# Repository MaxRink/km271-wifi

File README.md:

# KM271-WiFi (WiFi enabled replacement for the KM271)

If you just received a module, you can find help with installation here:

  - [Getting Started Guide](DOC/Getting_Started.md)
  - [Erste Schritte](DOC/Erste_Schritte.md)

This piece of hardware is a direct replacement for the Buderus KM271 to control a buderus heating system with Logamatic 2107 controller board. Maybe other controllers are supported. Please file an issue (or better a PR) if you have my module running in other Buderus heating controllers, so I can add them here.

This hardware and its documentation is released under the *TAPR Open Hardware License* Version 1.0 (May 25, 2007). 
A [copy of the license](LICENSE.txt) is included here or can be accessed in multiple formats on [tapr.org](https://tapr.org/the-tapr-open-hardware-license/). 

For more details, have a look in the:

  * [hardware description](DOC/Hardware%20Description.md)
  * [interactive BOM](https://htmlpreview.github.io/?https://github.com/the78mole/km271-wifi/blob/main/KM217-WiFi/bom/ibom_0.1.0.html)

If you bought the board in my tindie store, you could find a how-to to get it running [here](https://the78mole.de/projects/km271-wifi-howto/)

## Extensions

There is now an Extension to add wired Ethernet to the board. The prototype already works, availability in tindie store will still take some time...

## Order at JLCPCB

Ready-to-upload files for v1.1.0 are in [`KM217-WiFi/production/`](KM217-WiFi/production/) and [`EXTENSIONS/ETH_W5500/production/`](EXTENSIONS/ETH_W5500/production/) (gerber zip, BOM, CPL with LCSC part numbers, iBOM).

| | Main board | ETH add-on |
|---|---|---|
| Layers / thickness | 2 / 1.6 mm | 2 / 1.6 mm |
| Surface finish | ENIG | HASL lead-free |
| Gold fingers | Yes | No |
| Beveling | No (recessed finger tongue, board < 50 mm) | No |
| Assembly | Standard PCBA, both sides | Standard PCBA, both sides |

Details (part swaps, JLC rule checklist, CPL rotation fixes, cost estimate): [DOC/JLCPCB-ordering.md](DOC/JLCPCB-ordering.md).

## Improvements / ToDo

 * Add a OneWire temperature Sensor on the board itself
 * Fix a minor bug with external I2C pull-up (tie them to PCA9306 selectable supply)

## Firmware Management

This project includes a comprehensive firmware management system for easy firmware updates and batch production:

### 🚀 Quick Start

```bash
cd FW
./setup-dev.sh                                    # Setup development environment
uv run scripts/flash_firmware.py                  # List available firmware
uv run scripts/flash_firmware.py blinkenlights    # Flash single device
```

### 📦 Available Firmware Options

- **blinkenlights** - Local PlatformIO test project for hardware validation  
- **km271-esphome** - ESPHome-based KM271 WiFi replacement ([the78mole/ESPhome-KM271-WiFi](https://github.com/the78mole/ESPhome-KM271-WiFi))
- **dewenni-km271** - Feature-rich KM271 firmware ([dewenni/ESP_Buderus_KM271](https://github.com/dewenni/ESP_Buderus_KM271))

All firmware images are automatically downloaded and prepared for flashing using the management scripts.

### 🏭 Batch Production

For manufacturing multiple units:

```bash
uv run scripts/flash_firmware.py blinkenlights --loop
```

- Flash device → Connect next device → Press any key to continue
- Press 'n' to stop and show statistics
- Supports both ESC and 'n' for stopping

### 📖 Documentation

See [`FW/README.md`](FW/README.md) for detailed firmware management documentation, including:

- Setup instructions
- Script usage examples  
- Troubleshooting guide
- Batch production workflows

## 5V Supply Calibration

I decided to set the multiplier very far off the actual value, to make it clear, that you need to calibrate it due to the inaccurate/bad design of the ESP32 ADC with a quite low input impedance and general error.
To calibrate the Buderus 5V voltage monitor, you need to first find out the YAML section of your ESPhome device. It should look like the following:

```yaml
  - platform: adc
    pin: 36
    unit_of_measurement: "V"
    name: "KM217 5V Supply"
    accuracy_decimals: 2
    update_interval: 5s
    attenuation: 6dB
    filters:
      - multiply: 28.1826
      - throttle_average: 60s
```

Now look at the readout of your sensor, say it is 47.3V and measure the real voltage of the 5V supply (e.g. Pin 1 to 7 on the sensor header), say you measure 4.9V. Use the multiplier from your YAML and do the following calculation:

    4.9V / 47.3V * 28.1826 = 2.9196

Replace the multiplier by the calculated value and you will get more exact values, close to the 5V.

## Additional Information

  - [Moles Blog - Reverse Engineering KM271](https://the78mole.de/reverse-engineering-the-buderus-km217/)
  - [Moles Blog - KM271-WiFi Project](https://the78mole.de/projects/km271-wifi-howto/)
  - [KM271-WiFi ESPhome Project (GitHub)](https://github.com/the78mole/ESPhome-KM271-WiFi)
  - [KM271-WiFi WebTools (Flashing)](https://the78mole.github.io/ESPhome-KM271-WiFi/)
  - [KM271-Firmware ESPhome Component (GitHub)](https://github.com/the78mole/esphome_components)

You can buy the module on [Tindie](https://www.tindie.com/products/the78mole/buderus-km217-wifi-replacement/) (if available).

## Star History

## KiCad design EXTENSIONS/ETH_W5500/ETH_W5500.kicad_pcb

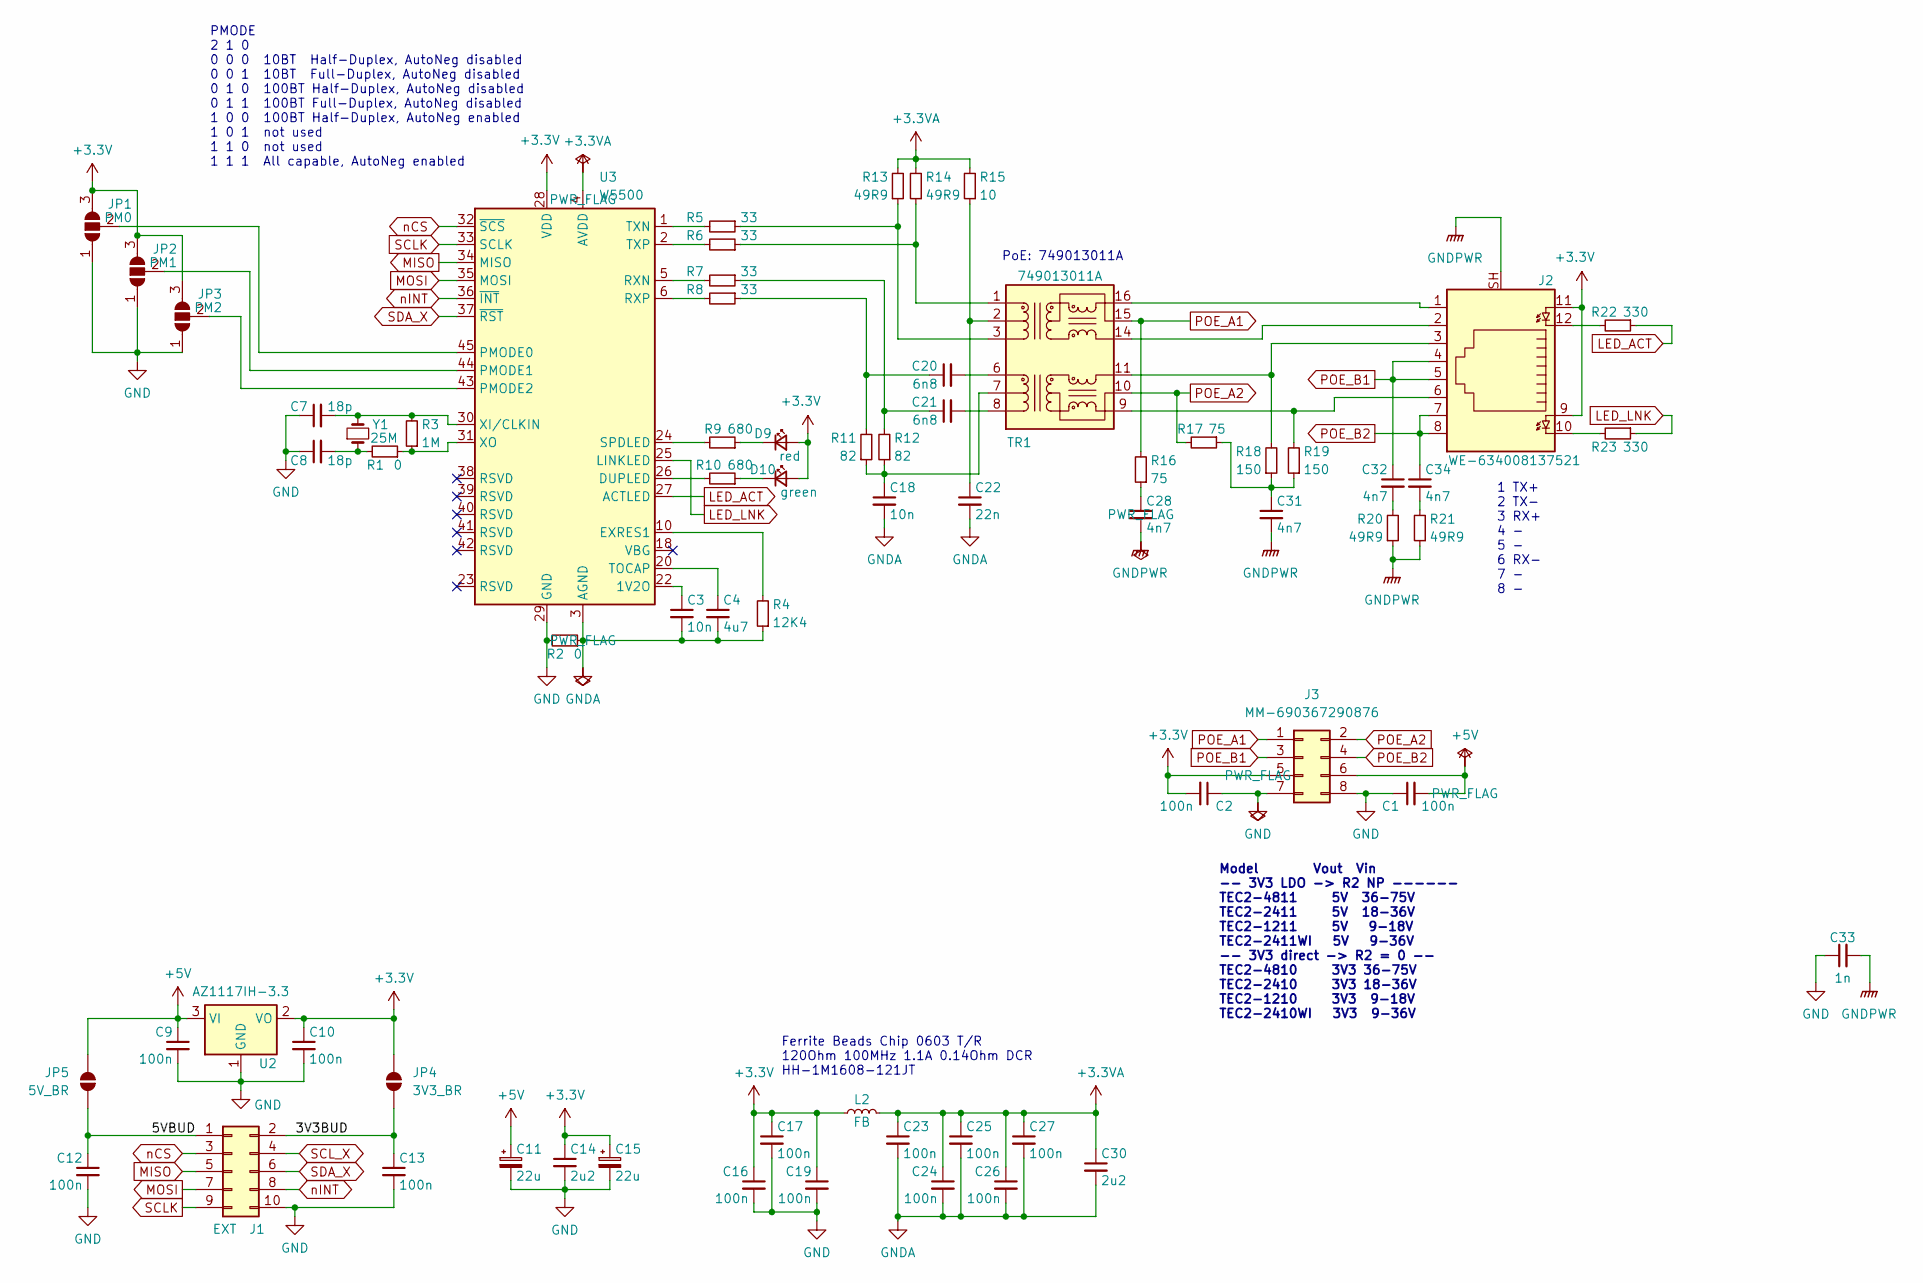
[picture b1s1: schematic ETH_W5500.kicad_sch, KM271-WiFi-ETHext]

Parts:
C1, C2, C9, C10, C12, C13, C16, C17, C19, C23, C24, C25, C26, C27: 100n; C_0603_1608Metric_Pad1.08x0.95mm_HandSolder; LCSC C14663
C3, C18: 10n; C_0603_1608Metric_Pad1.08x0.95mm_HandSolder; LCSC C57112
C4: 4u7; C_0805_2012Metric_Pad1.18x1.45mm_HandSolder; LCSC C1779
C7, C8: 18p; C_0603_1608Metric_Pad1.08x0.95mm_HandSolder; LCSC C1647
C11, C15: 22u; C_0805_2012Metric_Pad1.18x1.45mm_HandSolder; LCSC C45783
C14, C30: 2u2; C_0603_1608Metric_Pad1.08x0.95mm_HandSolder; LCSC C23630
C20, C21: 6n8; C_0603_1608Metric_Pad1.08x0.95mm_HandSolder; LCSC C1631
C22: 22n; C_0603_1608Metric_Pad1.08x0.95mm_HandSolder; LCSC C21122
C28, C31, C32, C34: 4n7; C_0603_1608Metric_Pad1.08x0.95mm_HandSolder; LCSC C53987
C33: 1n; C_1206_3216Metric_Pad1.33x1.80mm_HandSolder; LCSC C9196
D9: red; LED_0603_1608Metric_Pad1.05x0.95mm_HandSolder; LCSC C2286
D10: green; LED_0603_1608Metric_Pad1.05x0.95mm_HandSolder; LCSC C12624
J1: EXT; WE_PinSocket_TH_2x05_P2.54mm_Vertical_SMD; MPN 2.54-2*5P Female Header SMD; LCSC C843271
J2: WE-634008137521; WE-MJ-634008137521; LCSC C6095310
J3: MM-690367290876; WE-MM-690367290876; LCSC C20476862
JP1: PM0; SolderJumper-3_P1.3mm_Open_RoundedPad1.0x1.5mm_NumberLabels
JP2: PM1; SolderJumper-3_P1.3mm_Open_RoundedPad1.0x1.5mm_NumberLabels
JP3: PM2; SolderJumper-3_P1.3mm_Open_RoundedPad1.0x1.5mm_NumberLabels
JP4: 3V3_BR; SolderJumper-2_P1.3mm_Open_RoundedPad1.0x1.5mm
JP5: 5V_BR; SolderJumper-2_P1.3mm_Open_RoundedPad1.0x1.5mm
L2: FB; L_0805_2012Metric_Pad1.05x1.20mm_HandSolder; LCSC C1015
R1, R2: 0; L_0603_1608Metric_Pad1.05x0.95mm_HandSolder; LCSC C21189
R3: 1M; L_0603_1608Metric_Pad1.05x0.95mm_HandSolder; LCSC C22935
R4: 12K4; L_0603_1608Metric_Pad1.05x0.95mm_HandSolder; LCSC C177422
R5, R6, R7, R8: 33; L_0603_1608Metric_Pad1.05x0.95mm_HandSolder; LCSC C23140
R9, R10: 680; L_0603_1608Metric_Pad1.05x0.95mm_HandSolder; LCSC C23228
R11, R12: 82; L_0603_1608Metric_Pad1.05x0.95mm_HandSolder; LCSC C23255
R13, R14, R20, R21: 49R9; L_0603_1608Metric_Pad1.05x0.95mm_HandSolder; LCSC C23185
R15: 10; L_0603_1608Metric_Pad1.05x0.95mm_HandSolder; LCSC C22859
R16, R17: 75; L_0603_1608Metric_Pad1.05x0.95mm_HandSolder; LCSC C4275
R18, R19: 150; L_0603_1608Metric_Pad1.05x0.95mm_HandSolder; LCSC C22808
R22, R23: 330; L_0603_1608Metric_Pad1.05x0.95mm_HandSolder; LCSC C23138
TR1: 749013011A; Transformer_Ethernet_Wuerth_749013011A; LCSC C7193798
U2: AZ1117IH-3.3; SOT-223-3_TabPin2; MPN AZ1117IH-3.3TRG1; LCSC C108495
U3: W5500; LQFP-48_7x7mm_P0.5mm; LCSC C32843
Y1: 25M; Crystal_SMD_HC49-SD; MPN ABLS2-25.000MHZ-D4YF-T; LCSC C596824

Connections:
+3.3V: C2.2, C10.1, C14.1, C15.1, C16.1, C17.1, C19.1, D9.2 (A), D10.2 (A), J2.9, J2.11, J3.5, JP1.3 (B), JP2.3 (B), JP3.3 (B), JP4.1 (A), L2.1, U2.2 (VO), U3.28 (VDD)
+3.3VA: C23.1, C24.1, C25.1, C26.1, C27.1, C30.1, L2.2, R13.2, R14.2, R15.2, U3.4 (AVDD), U3.8 (AVDD), U3.11 (AVDD), U3.15 (AVDD), U3.17 (AVDD), U3.21 (AVDD)
+5V: C1.2, C9.1, C11.1, J3.6, JP5.1 (A), U2.3 (VI)
/3V3BUD: C13.1, J1.2, JP4.2 (B)
/5VBUD: C12.1, J1.1, JP5.2 (B)
GND: C1.1, C2.1, C7.1, C8.1, C9.2, C10.2, C11.2, C12.2, C13.2, C14.2, C15.2, C16.2, C17.2, C19.2, C33.1, J1.10, J3.7, J3.8, JP1.1 (A), JP2.1 (A), JP3.1 (A), R2.2, U2.1 (GND), U3.29 (GND)
GNDA: C3.2, C4.2, C18.2, C22.2, C23.2, C24.2, C25.2, C26.2, C27.2, C30.2, R2.1, R4.1, U3.3 (AGND), U3.9 (AGND), U3.14 (AGND), U3.16 (AGND), U3.19 (AGND), U3.48 (AGND)
GNDPWR: C28.2, C31.2, C33.2, J2.SH, R20.1, R21.1
LED_ACT: R22.1, U3.27 (ACTLED)
LED_LNK: R23.1, U3.25 (LINKLED)
MISO: J1.5, U3.34 (MISO)
MOSI: J1.7, U3.35 (MOSI)
unnamed: C8.2, R1.2, Y1.1
unnamed: C20.1, R8.1, R11.2
unnamed: C21.1, R7.1, R12.2
unnamed: C28.1, R16.1
unnamed: C31.1, R17.1, R18.1, R19.1
unnamed: C32.2, R20.2
unnamed: C34.2, R21.2
unnamed: D9.1 (K), R9.1
unnamed: D10.1 (K), R10.1
unnamed: J2.10, R23.2
unnamed: J2.12, R22.2
unnamed: JP1.2 (C), U3.45 (PMODE0)
unnamed: JP2.2 (C), U3.44 (PMODE1)
unnamed: JP3.2 (C), U3.43 (PMODE2)
unnamed: C18.1, R11.1, R12.1, TR1.7 (C_RD)
unnamed: C22.1, R15.1, TR1.2 (C_TD)
unnamed: C20.2, TR1.6 (RD+)
unnamed: C21.2, TR1.8 (RD-)
unnamed: J2.3, R18.2, TR1.11 (RX+)
unnamed: J2.6, R19.2, TR1.9 (RX-)
unnamed: R6.1, R14.1, TR1.1 (TD+)
unnamed: R5.1, R13.1, TR1.3 (TD-)
unnamed: J2.1, TR1.16 (TX+)
unnamed: J2.2, TR1.14 (TX-)
unnamed: C3.1, U3.22 (1V2O)
unnamed: R10.2, U3.26 (DUPLED)
unnamed: R4.2, U3.10 (EXRES1)
unnamed: R7.2, U3.5 (RXN)
unnamed: R8.2, U3.6 (RXP)
unnamed: R9.2, U3.24 (SPDLED)
unnamed: C4.1, U3.20 (TOCAP)
unnamed: R5.2, U3.1 (TXN)
unnamed: R6.2, U3.2 (TXP)
unnamed: C7.2, R3.2, U3.30 (XI/CLKIN), Y1.2
unnamed: R1.1, R3.1, U3.31 (XO)
POE_A1: J3.1, R16.2, TR1.15 (C_TX)
POE_A2: J3.2, R17.2, TR1.10 (C_RX)
POE_B1: C32.1, J2.4, J2.5, J3.3
POE_B2: C34.1, J2.7, J2.8, J3.4
SCLK: J1.9, U3.33 (SCLK)
SCL_X: J1.4
SDA_X: J1.6, U3.37 (~RST)
nCS: J1.3, U3.32 (~SCS)
nINT: J1.8, U3.36 (~INT)

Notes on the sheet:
PMODE 2 1 0 0 0 0 10BT Half-Duplex, AutoNeg disabled 0 0 1 10BT Full-Duplex, AutoNeg disabled 0 1 0 100BT Half-Duplex, AutoNeg disabled 0 1 1 100BT Full-Duplex, AutoNeg disabled 1 0 0 100BT Half-Duplex, AutoNeg enabled 1 0 1 not used 1 1 0 not used 1 1 1 All capable, AutoNeg enabled
PoE: 749013011A
Ferrite Beads Chip 0603 T/R 120Ohm 100MHz 1.1A 0.14Ohm DCR HH-1M1608-121JT
Model Vout Vin -- 3V3 LDO -> R2 NP ------ TEC2-4811 5V 36-75V TEC2-2411 5V 18-36V TEC2-1211 5V 9-18V TEC2-2411WI 5V 9-36V -- 3V3 direct -> R2 = 0 -- TEC2-4810 3V3 36-75V TEC2-2410 3V3 18-36V TEC2-1210 3V3 9-18V TEC2-2410WI 3V3 9-36V
1 TX+ 2 TX- 3 RX+ 4 - 5 - 6 RX- 7 - 8 -

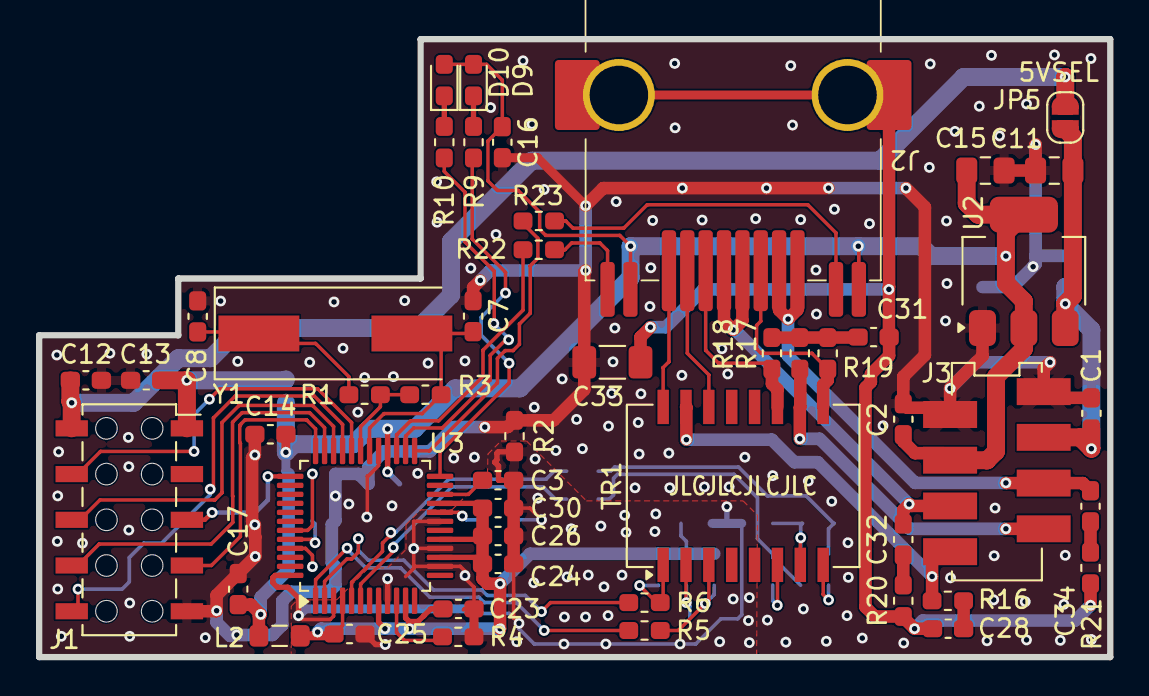
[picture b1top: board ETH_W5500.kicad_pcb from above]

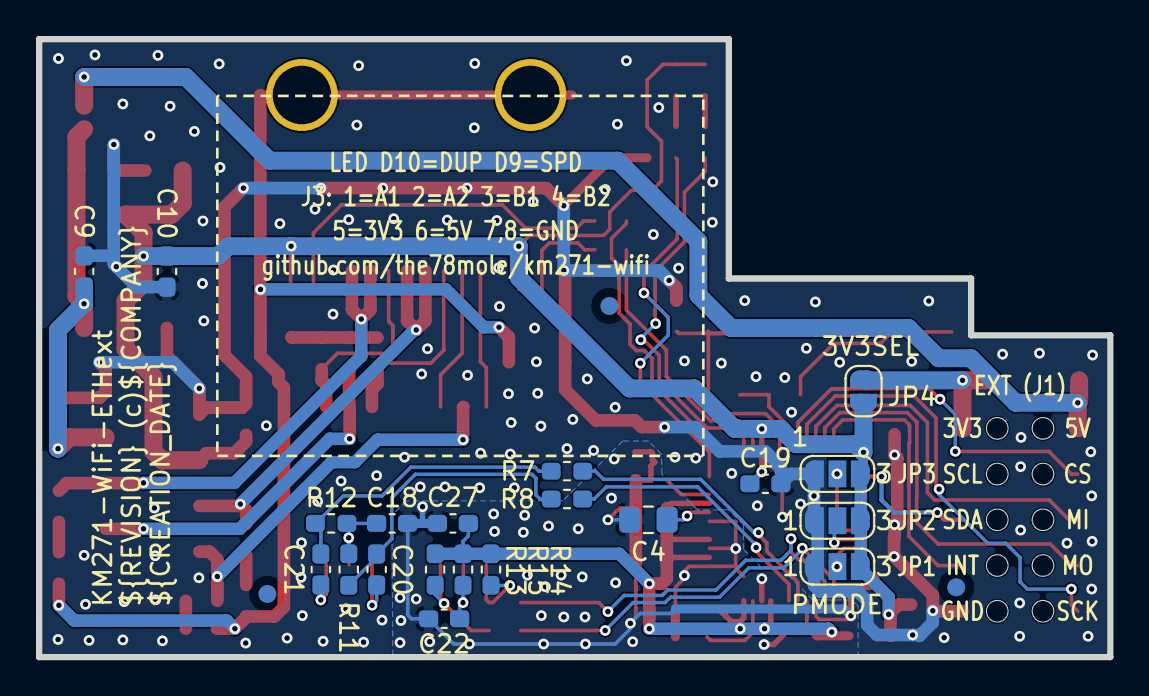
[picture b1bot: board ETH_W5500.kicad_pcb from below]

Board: 2 copper layers, 59.5 x 34.3 mm, 72 parts (23 on the bottom side), 55 nets.

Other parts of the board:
FID1, FID2, FID3: Fiducial_1mm_Mask2mm

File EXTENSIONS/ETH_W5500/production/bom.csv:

Designator,Footprint,Quantity,Value,LCSC Part #
"C1, C10, C12, C13, C16, C17, C19, C2, C23, C24, C25, C26, C27, C9",0603,14,100n,C14663
"C11, C15",0805,2,22u,C45783
"C14, C30",0603,2,2u2,C23630
"C18, C3",0603,2,10n,C57112
"C20, C21",0603,2,6n8,C1631
C22,0603,1,22n,C21122
"C28, C31, C32, C34",0603,4,4n7,C53987
C33,1206,1,1n,C9196
C4,0805,1,4u7,C1779
"C7, C8",0603,2,18p,C1647
D10,0603,1,green,C12624
D9,0603,1,red,C2286
J1,WE_PinSocket_TH_2x05_P2.54mm_Vertical_SMD,1,EXT,C843271
J2,WE-MJ-634008137521,1,WE-634008137521,C6095310
J3,WE-MM-690367290876,1,MM-690367290876,C20476862
L2,0805,1,FB,C1015
"R1, R2",0603,2,0,C21189
"R10, R9",0603,2,680,C23228
"R11, R12",0603,2,82,C23255
"R13, R14, R20, R21",0603,4,49R9,C23185
R15,0603,1,10,C22859
"R16, R17",0603,2,75,C4275
"R18, R19",0603,2,150,C22808
"R22, R23",0603,2,330,C23138
R3,0603,1,1M,C22935
R4,0603,1,12K4,C177422
"R5, R6, R7, R8",0603,4,33,C23140
TR1,Transformer_Ethernet_Wuerth_749013011A,1,749013011A,C7193798
U2,SOT-223-3_TabPin2,1,AZ1117IH-3.3,C108495
U3,LQFP-48_7x7mm_P0.5mm,1,W5500,C32843
Y1,Crystal_SMD_HC49-SD,1,25M,C596824

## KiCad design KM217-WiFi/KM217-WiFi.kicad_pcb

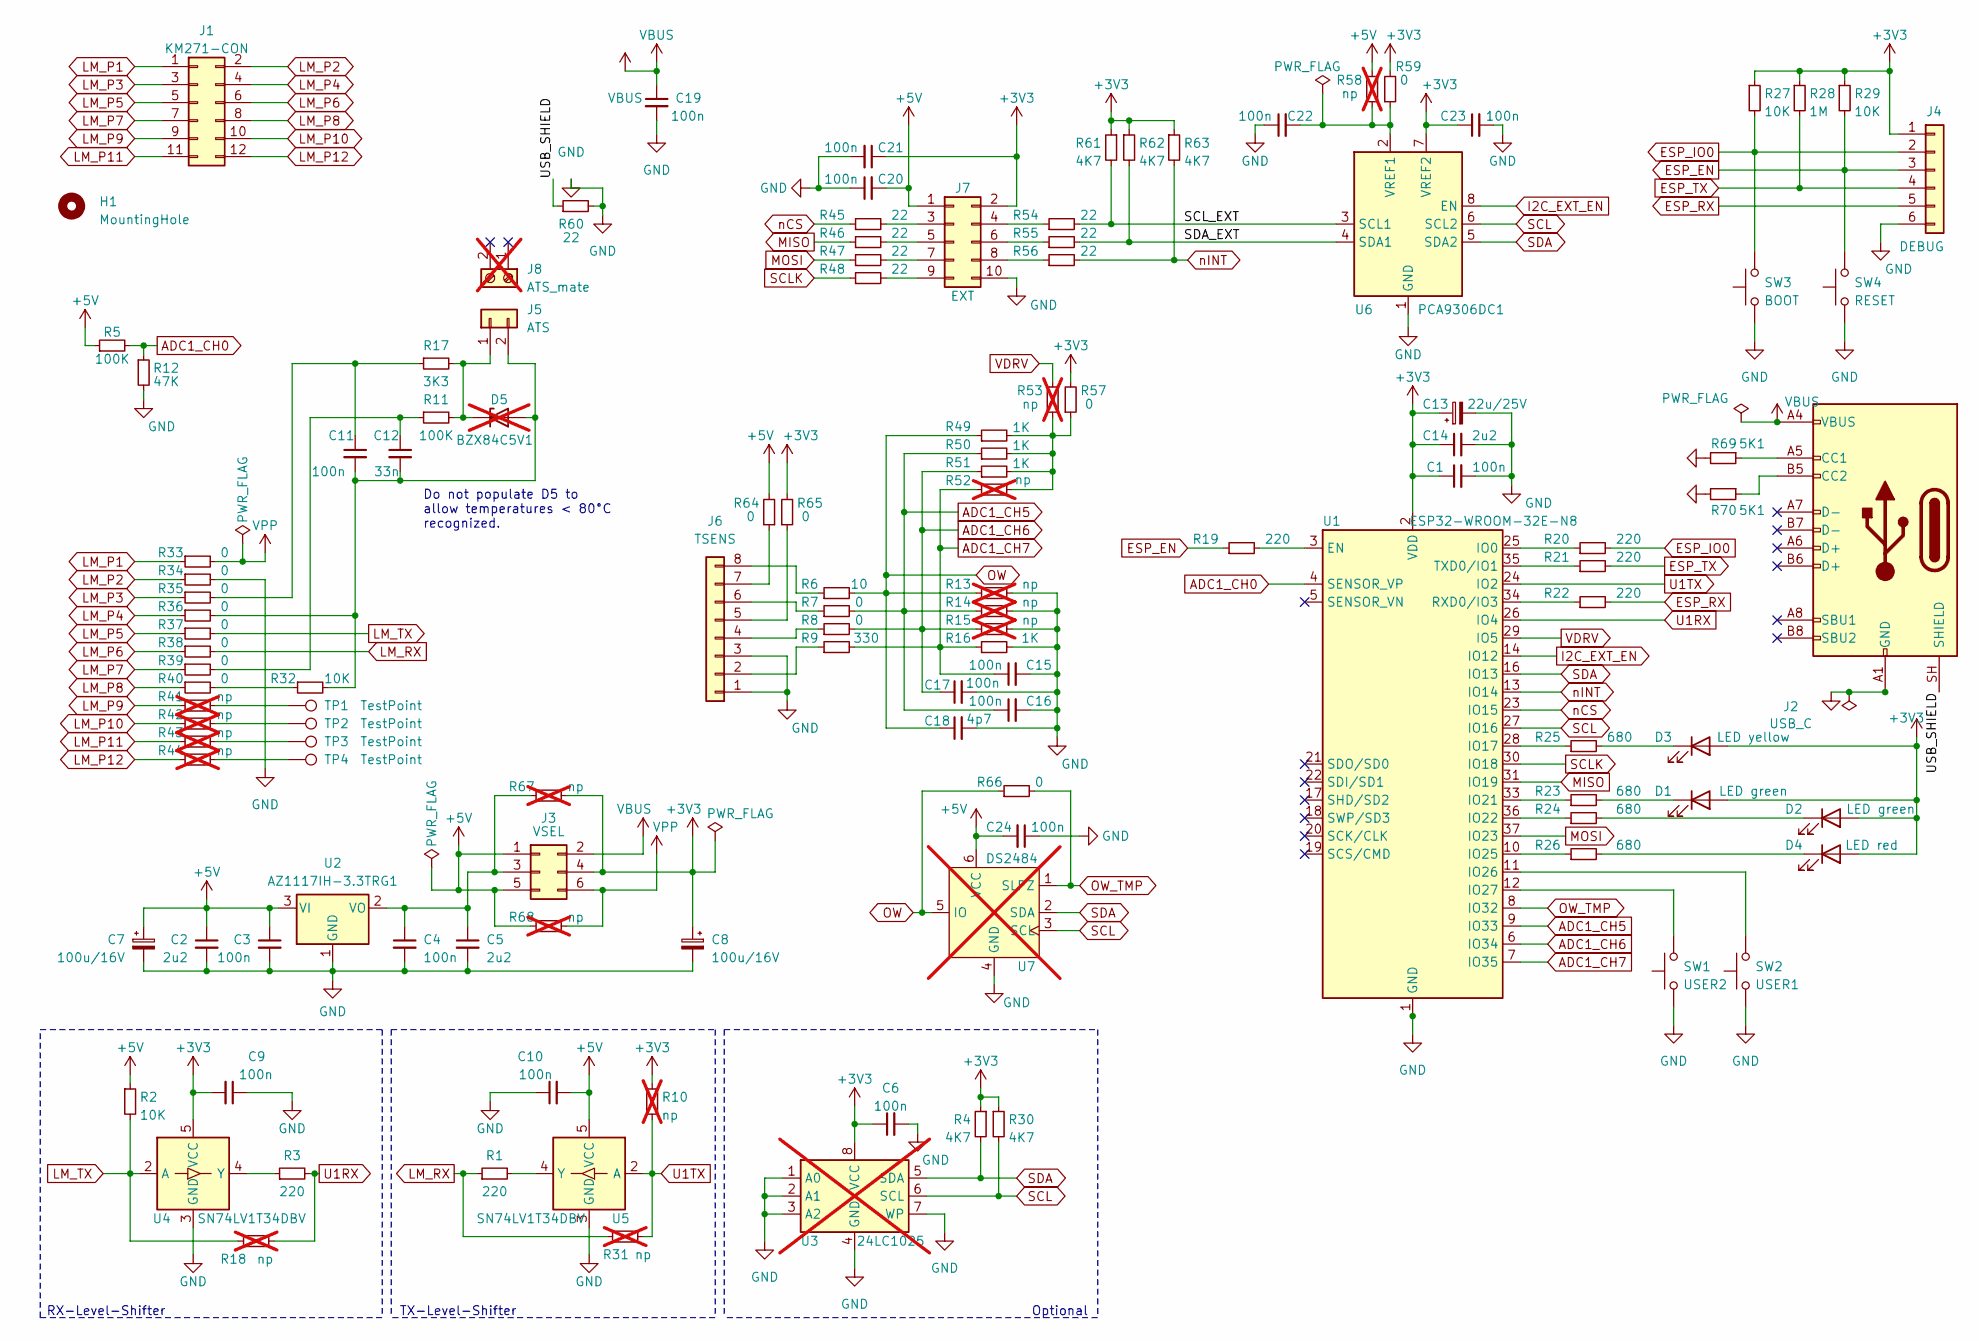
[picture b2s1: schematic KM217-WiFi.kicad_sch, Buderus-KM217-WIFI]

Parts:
C1, C3, C4, C6, C9, C10, C11, C15, C16, C17, C19, C20, C21, C22, C23, C24: 100n; C_0603_1608Metric_Pad1.08x0.95mm_HandSolder; MPN C0603_100n; LCSC C14663
C2, C5, C14: 2u2; C_0603_1608Metric_Pad1.08x0.95mm_HandSolder; MPN C0603_2u2; LCSC C23630
C7, C8: 100u/16V; CP_Elec_6.3x5.4_Nichicon; MPN UWT1C101MCL1GB; LCSC C340722
C12: 33n; C_0603_1608Metric_Pad1.08x0.95mm_HandSolder; MPN C0603_33n; LCSC C21117
C13: 22u/25V; C_1812_4532Metric_Pad1.57x3.40mm_HandSolder; MPN C4532X7R1E226MT000N; LCSC C76690
C18: 4p7; C_0603_1608Metric_Pad1.08x0.95mm_HandSolder; MPN C0603_4p7; LCSC C1669
D1, D2: LED green; LED_0603_1608Metric_Pad1.05x0.95mm_HandSolder; MPN D0603_LED_green; LCSC C12624
D3: LED yellow; LED_0603_1608Metric_Pad1.05x0.95mm_HandSolder; MPN D0603_LED_yellow; LCSC C2287
D4: LED red; LED_0603_1608Metric_Pad1.05x0.95mm_HandSolder; MPN D0603_LED_red; LCSC C2286
D5: BZX84C5V1; D_SOT-23_ANK; MPN BZX84C5V1-7-F; Digikey BZX84C5V1-7-F; not fitted
H1: MountingHole; MountingHole_3.2mm_M3_DIN965
J1: KM271-CON; LM2107_ComModuleCon; MPN PCB gold fingers
J2: USB_C; USB_C_Receptacle_HRO_TYPE-C-31-M-12; MPN TYPE-C-31-M-12; LCSC C165948
J3: VSEL; PinHeader_2x03_P2.54mm_Vertical_SMD; MPN HX PZ2.54-2x3P TP; LCSC C32713283
J4: DEBUG; PinHeader_2x03_P2.54mm_Horizontal; MPN HX PZ2.54-2x3P WC-A; LCSC C41417351
J5: ATS; PhoenixContact_MSTBA_2,5_2-G-5,08_1x02_P5.08mm_Horizontal; MPN 1757242; LCSC C90074
J6: TSENS; WAGO 2086-1208; MPN 2086-1208; LCSC C6074290
J7: EXT; PinHeader_2x05_P2.54mm_Vertical_SMD; MPN 54202-G0805LF; LCSC C3330868
J8: ATS_mate; MPN CTB9202/2; not fitted
R1, R3, R19, R20, R21, R22: 220; R_0603_1608Metric_Pad0.98x0.95mm_HandSolder; MPN R0603_220; LCSC C22962
R2, R27, R29, R32: 10K; R_0603_1608Metric_Pad0.98x0.95mm_HandSolder; MPN R0603_10K; LCSC C25804
R4, R30, R61, R62, R63: 4K7; R_0603_1608Metric_Pad0.98x0.95mm_HandSolder; MPN R0603_4K7; LCSC C23162
R5, R11: 100K; R_0603_1608Metric_Pad0.98x0.95mm_HandSolder; MPN R0603_100K; LCSC C25803
R6: 10; R_0603_1608Metric_Pad0.98x0.95mm_HandSolder; MPN R0603_10; LCSC C22859
R7, R8, R33, R34, R35, R36, R37, R38, R39, R40, R57, R59, R64, R65, R66: 0; R_0603_1608Metric_Pad0.98x0.95mm_HandSolder; MPN R0603_0; LCSC C21189
R9: 330; R_0603_1608Metric_Pad0.98x0.95mm_HandSolder; MPN R0603_330; LCSC C23138
R10, R13, R14, R15, R18, R31, R41, R42, R43, R44, R52, R53, R58, R67, R68: np; R_0603_1608Metric_Pad0.98x0.95mm_HandSolder; MPN np; not fitted
R12: 47K; R_0603_1608Metric_Pad0.98x0.95mm_HandSolder; MPN R0603_47K; LCSC C25819
R16, R49, R50, R51: 1K; R_0603_1608Metric_Pad0.98x0.95mm_HandSolder; MPN R0603_1K; LCSC C21190
R17: 3K3; R_0603_1608Metric_Pad0.98x0.95mm_HandSolder; MPN R0603_3K3; LCSC C22978
R23, R24, R25, R26: 680; R_0603_1608Metric_Pad0.98x0.95mm_HandSolder; MPN R0603_680; LCSC C23228
R28: 1M; R_0603_1608Metric_Pad0.98x0.95mm_HandSolder; MPN R0603_1M; LCSC C22935
R45, R46, R47, R48, R54, R55, R56, R60: 22; R_0603_1608Metric_Pad0.98x0.95mm_HandSolder; MPN R0603_22; LCSC C23345
R69, R70: 5K1; R_0603_1608Metric_Pad0.98x0.95mm_HandSolder; LCSC C23186
SW1: USER2; SW_SPST_B3SL-1002P; MPN B3SL-1002P; LCSC C306880
SW2: USER1; SW_SPST_B3SL-1002P; MPN B3SL-1002P; LCSC C306880
SW3: BOOT; SW_SPST_B3SL-1002P; MPN B3SL-1002P; LCSC C306880
SW4: RESET; SW_SPST_B3SL-1002P; MPN B3SL-1002P; LCSC C306880
TP1, TP2, TP3, TP4: TestPoint; TestPoint_Pad_D2.0mm
U1: ESP32-WROOM-32E-N8; ESP32-WROOM-32; MPN ESP32-WROOM-32E-N8; LCSC C701342
U2: AZ1117IH-3.3TRG1; SOT-223-3_TabPin2; MPN AZ1117IH-3.3TRG1; LCSC C108495
U3: 24LC1025; SO-8_5.3x6.2mm_P1.27mm; MPN 24LC1025-I/SM; not fitted
U4, U5: SN74LV1T34DBV; SOT-23-5; MPN SN74LV1T34DBVR; LCSC C100024
U6: PCA9306DC1; VSSOP-8_2.3x2mm_P0.5mm; MPN PCA9306DC1Z; LCSC C5119911
U7: DS2484; SOT-23-6_Handsoldering; MPN DS2484R+T; Digikey DS2484R+T; not fitted

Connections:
+3V3: C1.1, C6.1, C8.1, C9.2, C13.1, C14.1, C21.1, C23.1, D1.2 (A), D2.2 (A), D3.2 (A), D4.2 (A), J3.4, J4.1, J7.2, R4.1, R10.1, R27.1, R28.1, R29.1, R30.1, R57.2, R59.2, R61.1, R62.1, R63.1, R65.2, R67.2, U1.2 (VDD), U3.8 (VCC), U4.5 (VCC), U6.7 (VREF2)
+5V: C2.1, C3.1, C7.1, C10.2, C20.2, C24.2, J3.1, J3.5, J7.1, R2.1, R5.1, R58.2, R64.2, R68.1, U2.3 (VI), U5.5 (VCC), U7.6 (VCC)
/SCL_EXT: R54.2, R61.2, U6.3 (SCL1)
/SDA_EXT: R55.2, R62.2, U6.4 (SDA1)
/USB_SHIELD: J2.SH (SHIELD), R60.1
ADC1_CH0: R5.2, R12.1, U1.4 (SENSOR_VP)
ADC1_CH5: C16.1, R7.2, R14.1, R50.1, U1.9 (IO33)
ADC1_CH6: C17.1, R8.2, R15.1, R51.1, U1.6 (IO34)
ADC1_CH7: C15.1, R9.2, R16.1, R52.1, U1.7 (IO35)
ESP_EN: J4.3, R19.1, R29.2, SW4.2
ESP_IO0: J4.2, R20.2, R27.2, SW3.2
ESP_RX: J4.5, R22.2
ESP_TX: J4.4, R21.2, R28.2
GND: C1.2, C2.2, C3.2, C4.2, C5.2, C6.2, C7.2, C8.2, C9.1, C10.1, C13.2, C14.2, C15.2, C16.2, C17.2, C18.2, C19.2, C20.1, C21.2, C22.1, C23.2, C24.1, J2.A1 (GND), J2.A12 (GND), J2.B1 (GND), J2.B12 (GND), J4.6, J6.1, J6.3, J7.10, R12.2, R13.2, R14.2, R15.2, R16.2, R34.2, R60.2, R69.2, R70.2, SW1.1, SW2.1, SW3.1, SW4.1, U1.1 (GND), U1.15 (GND), U1.38 (GND), U1.39 (GND), U2.1 (GND), U3.1 (A0), U3.2 (A1), U3.3 (A2), U3.4 (GND), U3.7 (WP), U4.3 (GND), U5.3 (GND), U6.1 (GND), U7.4 (GND)
I2C_EXT_EN: U1.14 (IO12), U6.8 (EN)
LM_P1: J1.1, R33.1
LM_P2: J1.2, R34.1
LM_P3: J1.3, R35.1
LM_P4: J1.4, R36.1
LM_P5: J1.5, R37.1
LM_P6: J1.6, R38.1
LM_P7: J1.7, R39.1
LM_P8: J1.8, R40.1
LM_P9: J1.9, R41.1
LM_P10: J1.10, R42.1
LM_P11: J1.11, R43.1
LM_P12: J1.12, R44.1
LM_RX: R1.1, R31.1, R38.2
LM_TX: R2.2, R18.1, R37.2, U4.2 (A)
MISO: R46.1, U1.31 (IO19)
MOSI: R47.1, U1.37 (IO23)
unnamed: C11.1, R17.1, R35.2
unnamed: C12.1, R11.1, R39.2
unnamed: D1.1 (K), R23.2
unnamed: D2.1 (K), R24.2
unnamed: D3.1 (K), R25.2
unnamed: D4.1 (K), R26.2
unnamed: C11.2, C12.2, D5.2 (A), J5.2, R32.2, R36.2
unnamed: D5.1 (K), J5.1, R11.2, R17.2
unnamed: J2.A5 (CC1), R69.1
unnamed: J2.B5 (CC2), R70.1
unnamed: C4.1, C5.1, J3.3, R67.1, U2.2 (VO)
unnamed: J6.2, R9.1
unnamed: J6.4, R8.1
unnamed: J6.5, R65.1
unnamed: J6.6, R7.1
unnamed: J6.7, R64.1
unnamed: J6.8, R6.1
unnamed: J7.3, R45.2
unnamed: J7.4, R54.1
unnamed: J7.5, R46.2
unnamed: J7.6, R55.1
unnamed: J7.7, R47.2
unnamed: J7.8, R56.1
unnamed: J7.9, R48.2
unnamed: R32.1, R40.2
unnamed: R41.2, TP1.1
unnamed: R42.2, TP2.1
unnamed: R43.2, TP3.1
unnamed: R44.2, TP4.1
unnamed: R49.2, R50.2, R51.2, R52.2, R53.1, R57.1
unnamed: R19.2, U1.3 (EN)
unnamed: R20.1, U1.25 (IO0)
unnamed: R25.1, U1.28 (IO17)
unnamed: R23.1, U1.33 (IO21)
unnamed: R24.1, U1.36 (IO22)
unnamed: R26.1, U1.10 (IO25)
unnamed: SW2.2, U1.11 (IO26)
unnamed: SW1.2, U1.12 (IO27)
unnamed: R22.1, U1.34 (RXD0/IO3)
unnamed: R21.1, U1.35 (TXD0/IO1)
unnamed: R3.1, U4.4 (Y)
unnamed: R1.2, U5.4 (Y)
unnamed: C22.2, R58.1, R59.1, U6.2 (VREF1)
OW: C18.1, R6.2, R13.1, R49.1, R66.1, U7.5 (IO)
OW_TMP: R66.2, U1.8 (IO32), U7.1 (SLPZ)
SCL: R30.2, U1.27 (IO16), U3.6 (SCL), U6.6 (SCL2), U7.3 (SCL)
SCLK: R48.1, U1.30 (IO18)
SDA: R4.2, U1.16 (IO13), U3.5 (SDA), U6.5 (SDA2), U7.2 (SDA)
U1RX: R3.2, R18.2, U1.26 (IO4)
U1TX: R10.2, R31.2, U1.24 (IO2), U5.2 (A)
VBUS: C19.1, J2.A4 (VBUS), J2.A9 (VBUS), J2.B4 (VBUS), J2.B9 (VBUS), J3.2
VDRV: R53.2, U1.29 (IO5)
VPP: J3.6, R33.2, R68.2
nCS: R45.1, U1.23 (IO15)
nINT: R56.2, R63.2, U1.13 (IO14)

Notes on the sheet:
RX-Level-Shifter
TX-Level-Shifter
Optional
Do not populate D5 to allow temperatures < 80°C recognized.

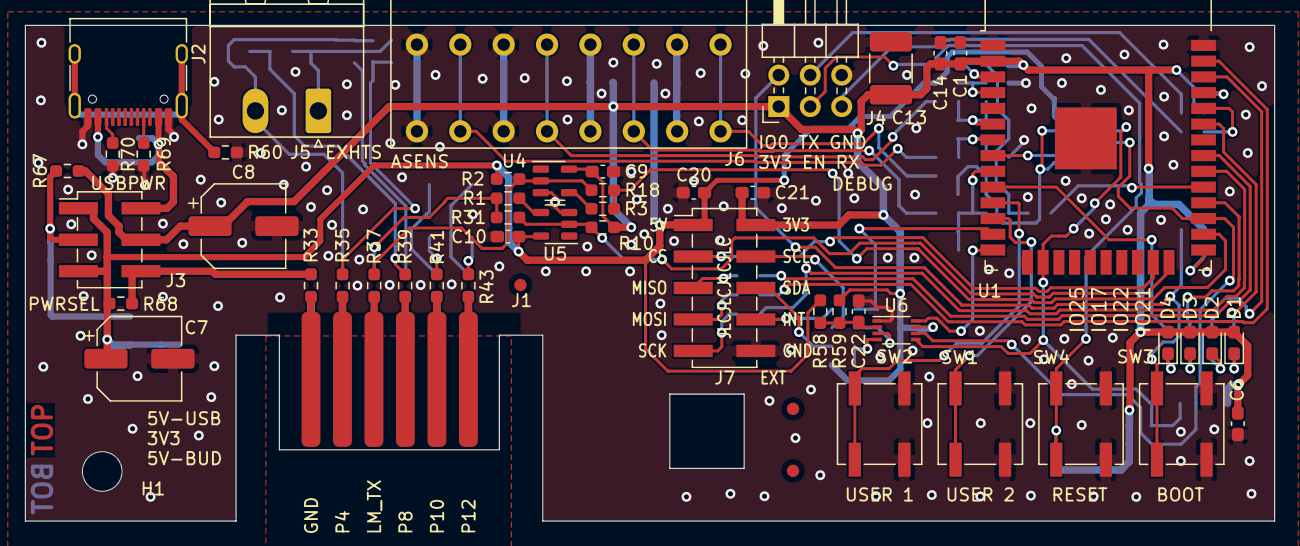
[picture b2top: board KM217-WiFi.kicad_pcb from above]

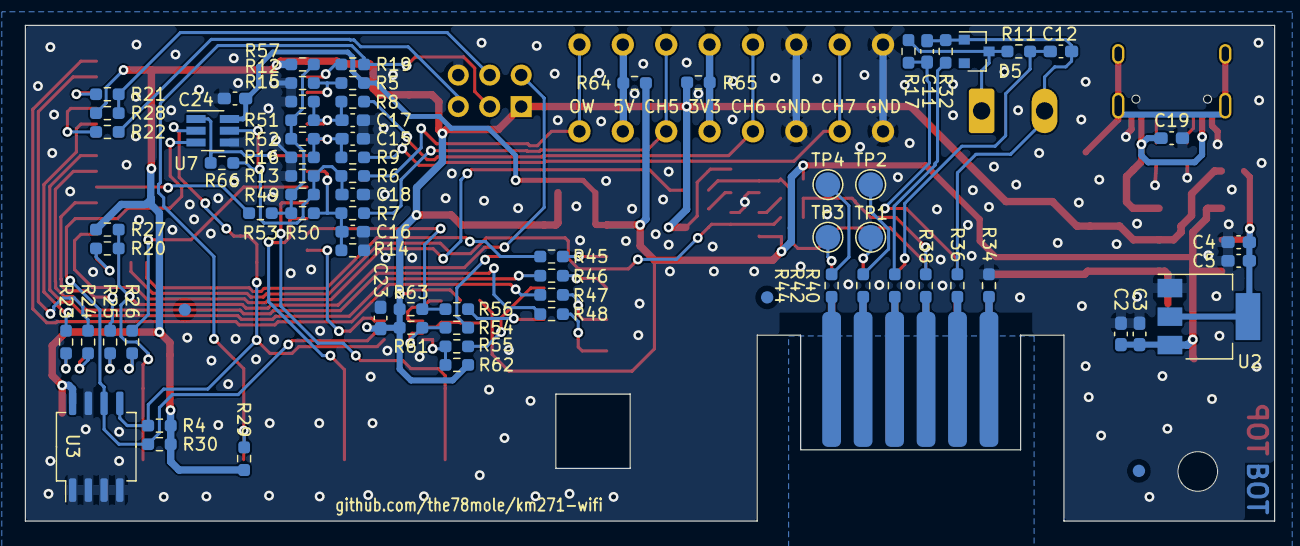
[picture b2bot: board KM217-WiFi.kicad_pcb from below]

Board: 2 copper layers, 100.8 x 40.0 mm, 128 parts (75 on the bottom side), 86 nets.

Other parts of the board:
FID1, FID2, FID3, FID4, FID5, FID6: Fiducial_1mm_Mask2mm

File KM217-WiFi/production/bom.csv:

Designator,Footprint,Quantity,Value,LCSC Part #
"C1, C10, C11, C15, C16, C17, C19, C20, C21, C22, C23, C24, C3, C4, C6, C9",0603,16,100n,C14663
C12,0603,1,33n,C21117
C13,1812,1,22u/25V,C76690
"C14, C2, C5",0603,3,2u2,C23630
C18,0603,1,4p7,C1669
"C7, C8",CP_Elec_6.3x5.4_Nichicon,2,100u/16V,C340722
"D1, D2",0603,2,LED green,C12624
D3,0603,1,LED yellow,C2287
D4,0603,1,LED red,C2286
J2,USB_C_Receptacle_HRO_TYPE-C-31-M-12,1,USB_C,C165948
J3,PinHeader_2x03_P2.54mm_Vertical_SMD,1,VSEL,C32713283
J7,PinHeader_2x05_P2.54mm_Vertical_SMD,1,EXT,C3330868
"R1, R19, R20, R21, R22, R3",0603,6,220,C22962
"R11, R5",0603,2,100K,C25803
R12,0603,1,47K,C25819
"R16, R49, R50, R51",0603,4,1K,C21190
R17,0603,1,3K3,C22978
"R2, R27, R29, R32",0603,4,10K,C25804
"R23, R24, R25, R26",0603,4,680,C23228
R28,0603,1,1M,C22935
"R30, R4, R61, R62, R63",0603,5,4K7,C23162
"R33, R34, R35, R36, R37, R38, R39, R40, R57, R59, R64, R65, R66, R7, R8",0603,15,0,C21189
"R45, R46, R47, R48, R54, R55, R56, R60",0603,8,22,C23345
R6,0603,1,10,C22859
"R69, R70",0603,2,5K1,C23186
R9,0603,1,330,C23138
SW3,SW_SPST_B3SL-1002P,1,BOOT,C306880
SW4,SW_SPST_B3SL-1002P,1,RESET,C306880
U1,ESP32-WROOM-32,1,ESP32-WROOM-32E-N8,C701342
U2,SOT-223-3_TabPin2,1,AZ1117IH-3.3TRG1,C108495
"U4, U5",SOT-23-5,2,SN74LV1T34DBV,C100024
U6,VSSOP-8_2.3x2mm_P0.5mm,1,PCA9306DC1,C5119911
